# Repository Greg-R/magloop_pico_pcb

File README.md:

#  Printed Circuit Board for Magnetic Loop Antenna Controller

**Please note this repository is no longer active.**

The new repository is here:

(https://github.com/Greg-R/magloop_pico_pcb_2)

Design and fabrication files the Magnetic Loop Antenna Controller printed circuit board.

#  License

Please refer to the LICENSE file included in this repository.

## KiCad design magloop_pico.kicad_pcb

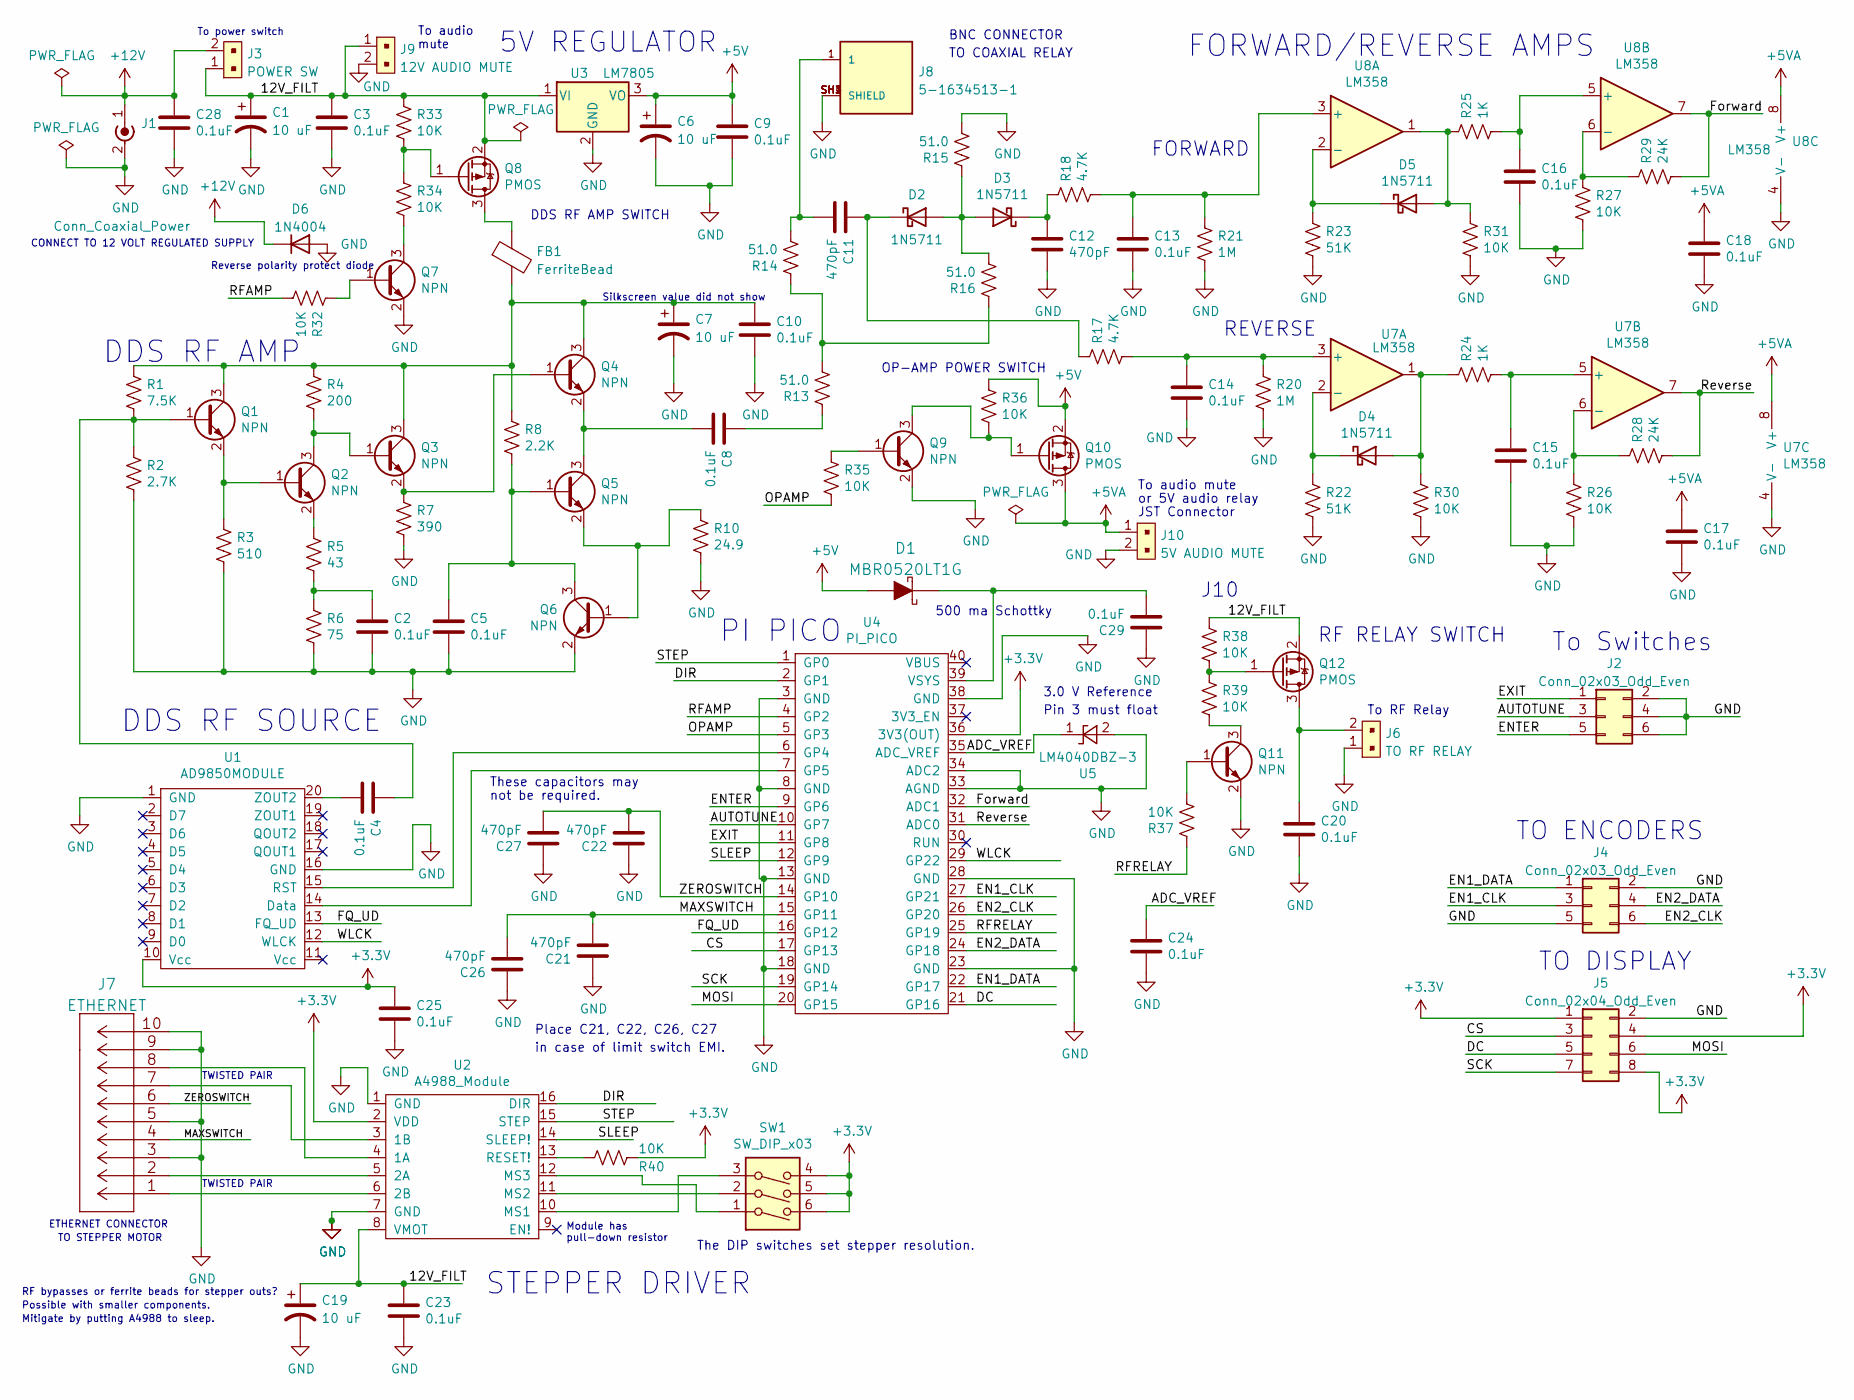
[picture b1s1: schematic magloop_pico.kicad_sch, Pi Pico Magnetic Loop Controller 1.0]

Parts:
C1, C6, C7, C19: 10 uF; CP_Radial_D5.0mm_P2.00mm
C2, C3, C4, C5, C8, C9, C10, C13, C14, C15, C16, C17, C18, C20, C23, C24, C25, C28, C29: 0.1uF; C_1206_3216Metric_Pad1.33x1.80mm_HandSolder
C11, C12, C21, C22, C26, C27: 470pF; C_1206_3216Metric_Pad1.33x1.80mm_HandSolder
D1: MBR0520LT1G; SOD-123; MPN MBR0520LT1G; Digi-Key_PN MBR0520LT1GOSCT-ND
D2, D3, D4, D5: 1N5711; D_DO-35_SOD27_P7.62mm_Horizontal
D6: 1N4004; D_SMB
FB1: FerriteBead; L_1206_3216Metric
J1: Conn_Coaxial_Power; BarrelJack_CUI_PJ-036AH-SMT_Horizontal
J2, J4: Conn_02x03_Odd_Even; IDC-Header_2x03_P2.54mm_Vertical
J3: POWER SW; PinHeader_1x2_P2.5mm_Drill1.1mm; MPN B2B-XH-A(LF)(SN); Digi-Key_PN 455-2247-ND
J5: Conn_02x04_Odd_Even; IDC-Header_2x04_P2.54mm_Vertical
J6: TO RF RELAY; PinHeader_1x2_P2.5mm_Drill1.1mm; MPN B2B-XH-A(LF)(SN); Digi-Key_PN 455-2247-ND
J7: ETHERNET; 2-406541-3
J8: 5-1634513-1; TE_5-1634513-1
J9: 12V AUDIO MUTE; PinHeader_1x2_P2.5mm_Drill1.1mm; MPN B2B-XH-A(LF)(SN); Digi-Key_PN 455-2247-ND
J10: 5V AUDIO MUTE; PinHeader_1x2_P2.5mm_Drill1.1mm; MPN B2B-XH-A(LF)(SN); Digi-Key_PN 455-2247-ND
Q1, Q2, Q3, Q4, Q5, Q6, Q7, Q9, Q11: NPN; SOT-23_Handsoldering
Q8, Q10, Q12: PMOS; SOT-23_Handsoldering
R1: 7.5K; R_1206_3216Metric_Pad1.30x1.75mm_HandSolder
R2: 2.7K; R_1206_3216Metric_Pad1.30x1.75mm_HandSolder
R3: 510; R_1206_3216Metric_Pad1.30x1.75mm_HandSolder
R4: 200; R_1206_3216Metric_Pad1.30x1.75mm_HandSolder
R5: 43; R_1206_3216Metric_Pad1.30x1.75mm_HandSolder
R6: 75; R_1206_3216Metric_Pad1.30x1.75mm_HandSolder
R7: 390; R_1206_3216Metric_Pad1.30x1.75mm_HandSolder
R8: 2.2K; R_1206_3216Metric_Pad1.30x1.75mm_HandSolder
R10: 24.9; R_1206_3216Metric_Pad1.30x1.75mm_HandSolder
R13, R14, R15, R16: 51.0; R_1206_3216Metric_Pad1.30x1.75mm_HandSolder
R17, R18: 4.7K; R_1206_3216Metric_Pad1.30x1.75mm_HandSolder
R20, R21: 1M; R_1206_3216Metric_Pad1.30x1.75mm_HandSolder
R22, R23: 51K; R_1206_3216Metric_Pad1.30x1.75mm_HandSolder
R24, R25: 1K; R_1206_3216Metric_Pad1.30x1.75mm_HandSolder
R26, R27, R30, R31, R32, R33, R34, R35, R36, R37, R38, R39, R40: 10K; R_1206_3216Metric_Pad1.30x1.75mm_HandSolder
R28, R29: 24K; R_1206_3216Metric_Pad1.30x1.75mm_HandSolder
SW1: SW_DIP_x03; DIP-6_W7.62mm
U1: AD9850MODULE; AD9850_MODULE
U2: A4988_Module; A4988_MODULE
U3: LM7805; TO-220-3_Vertical
U4: PI_PICO
U5: LM4040DBZ-3; SOT-23_Handsoldering
U7, U8: LM358; DIP-8_W7.62mm

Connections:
+3V3: C25.1, J5.1, J5.4, J5.8, R40.1, SW1.4, SW1.5, SW1.6, U1.10 (Vcc), U2.2 (VDD), U4.36 (3V3(OUT))
+5V: C6.1, C9.1, D1.A, Q10.2 (S), R36.1, U3.3 (VO)
+5VA: C17.1, C18.1, J10.1, Q10.3 (D), U7.8 (V+), U8.8 (V+)
+12V: C28.1, D6.1 (K), J1.1 (In), J3.2
/12V_FILT: C1.1, C3.1, C19.1, C23.1, J3.1, J9.1, Q8.2 (S), Q12.2 (S), R33.1, R38.1, U2.8 (VMOT), U3.1 (VI)
/ADC_VREF: C24.1, U4.35 (ADC_VREF), U5.1 (K)
/AUTOTUNE: J2.3, U4.10 (GP7)
/CS: J5.3, U4.17 (GP13)
/DC: J5.5, U4.21 (GP16)
/DIR: U2.16 (DIR), U4.2 (GP1)
/EN1_CLK: J4.3, U4.27 (GP21)
/EN1_DATA: J4.1, U4.22 (GP17)
/EN2_CLK: J4.6, U4.26 (GP20)
/EN2_DATA: J4.4, U4.24 (GP18)
/ENTER: J2.5, U4.9 (GP6)
/EXIT: J2.1, U4.11 (GP8)
/FQ_UD: U1.13 (FQ_UD), U4.16 (GP12)
/Forward: R29.2, U4.32 (ADC1), U8.7
/MAXSWITCH: C21.2, C26.2, J7.4, U4.15 (GP11)
/MOSI: J5.6, U4.20 (GP15)
/OPAMP: R35.2, U4.5 (GP3)
/RFAMP: R32.2, U4.4 (GP2)
/RFRELAY: R37.1, U4.25 (GP19)
/Reverse: R28.2, U4.31 (ADC0), U7.7
/SCK: J5.7, U4.19 (GP14)
/SLEEP: U2.14 (SLEEP!), U4.12 (GP9)
/STEP: U2.15 (STEP), U4.1 (GP0)
/WLCK: U1.12 (WLCK), U4.29 (GP22)
/ZEROSWITCH: C22.2, C27.2, J7.6, U4.14 (GP10)
GND: C1.2, C2.2, C3.2, C5.2, C6.2, C7.2, C9.2, C10.2, C12.2, C13.2, C14.2, C15.2, C16.2, C17.2, C18.2, C19.2, C20.2, C21.1, C22.1, C23.2, C24.2, C25.2, C26.1, C27.1, C28.2, C29.1, D6.2 (A), J1.2 (Ext), J2.2, J2.4, J2.6, J4.2, J4.5, J5.2, J6.1, J7.3, J7.5, J7.9, J7.10, J8.SH1 (SHIELD), J8.SH2 (SHIELD), J8.SH3 (SHIELD), J8.SH4 (SHIELD), J9.2, J10.2, Q6.2 (E), Q7.2 (E), Q9.2 (E), Q11.2 (E), R2.2, R3.2, R6.2, R7.2, R10.2, R15.2, R20.2, R21.2, R22.2, R23.2, R26.2, R27.2, R30.2, R31.2, U1.1 (GND), U1.16 (GND), U2.1 (GND), U2.7 (GND), U3.2 (GND), U4.3 (GND), U4.8 (GND), U4.13 (GND), U4.18 (GND), U4.23 (GND), U4.28 (GND), U4.33 (AGND), U4.34 (ADC2), U4.38 (GND), U5.2 (A), U7.4 (V-), U8.4 (V-)
unnamed: C2.1, R5.2, R6.1
unnamed: C4.1, Q1.1 (B), R1.2, R2.1
unnamed: C4.2, U1.20 (ZOUT2)
unnamed: C5.1, Q5.1 (B), Q6.3 (C), R8.2
unnamed: C8.1, R13.1
unnamed: C8.2, Q4.2 (E), Q5.3 (C)
unnamed: C7.1, C10.1, FB1.2, Q1.3 (C), Q3.3 (C), Q4.3 (C), R1.1, R4.1, R8.1
unnamed: C11.1, D2.1 (K), R17.1
unnamed: C11.2, J8.1, R14.2
unnamed: C12.1, D3.1 (K), R18.1
unnamed: C13.1, R18.2, R21.1, U8.3 (+)
unnamed: C14.1, R17.2, R20.1, U7.3 (+)
unnamed: C15.1, R24.2, U7.5 (+)
unnamed: C16.1, R25.2, U8.5 (+)
unnamed: C20.1, J6.2, Q12.3 (D)
unnamed: C29.2, D1.K, U4.39 (VSYS)
unnamed: D2.2 (A), D3.2 (A), R15.1, R16.2
unnamed: D4.1 (K), R22.1, U7.2 (-)
unnamed: D4.2 (A), R24.1, R30.1, U7.1
unnamed: D5.1 (K), R23.1, U8.2 (-)
unnamed: D5.2 (A), R25.1, R31.1, U8.1
unnamed: FB1.1, Q8.3 (D)
unnamed: J7.1, U2.6 (2B)
unnamed: J7.2, U2.5 (2A)
unnamed: J7.7, U2.3 (1B)
unnamed: J7.8, U2.4 (1A)
unnamed: Q1.2 (E), Q2.1 (B), R3.1
unnamed: Q2.2 (E), R5.1
unnamed: Q2.3 (C), Q3.1 (B), R4.2
unnamed: Q3.2 (E), Q4.1 (B), R7.1
unnamed: Q5.2 (E), Q6.1 (B), R10.1
unnamed: Q7.1 (B), R32.1
unnamed: Q7.3 (C), R34.2
unnamed: Q8.1 (G), R33.2, R34.1
unnamed: Q9.1 (B), R35.1
unnamed: Q9.3 (C), Q10.1 (G), R36.2
unnamed: Q11.1 (B), R37.2
unnamed: Q11.3 (C), R39.2
unnamed: Q12.1 (G), R38.2, R39.1
unnamed: R13.2, R14.1, R16.1
unnamed: R26.1, R28.1, U7.6 (-)
unnamed: R27.1, R29.1, U8.6 (-)
unnamed: R40.2, U2.13 (RESET!)
unnamed: SW1.1, U2.12 (MS3)
unnamed: SW1.2, U2.11 (MS2)
unnamed: SW1.3, U2.10 (MS1)
unnamed: U1.14 (Data), U4.7 (GP5)
unnamed: U1.15 (RST), U4.6 (GP4)

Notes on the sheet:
To RF Relay
CONNECT TO 12 VOLT REGULATED SUPPLY
PI PICO
STEPPER DRIVER
To audio mute
JST Connector
The DIP switches set stepper resolution.
BNC CONNECTOR
To Switches
Reverse polarity protect diode
DDS RF AMP SWITCH
or 5V audio relay
TWISTED PAIR
ETHERNET CONNECTOR
Silkscreen value did not show
Module has pull-down resistor
TO STEPPER MOTOR
J10
RF bypasses or ferrite beads for stepper outs?
OP-AMP POWER SWITCH
5V REGULATOR
REVERSE
To audio
To power switch
DDS RF SOURCE
TO COAXIAL RELAY
Place C21, C22, C26, C27
TO ENCODERS
500 ma Schottky
FORWARD
DDS RF AMP
These capacitors may
Possible with smaller components.
TO DISPLAY
Mitigate by putting A4988 to sleep.
FORWARD/REVERSE AMPS
Pin 3 must float
3.0 V Reference
mute
not be required.

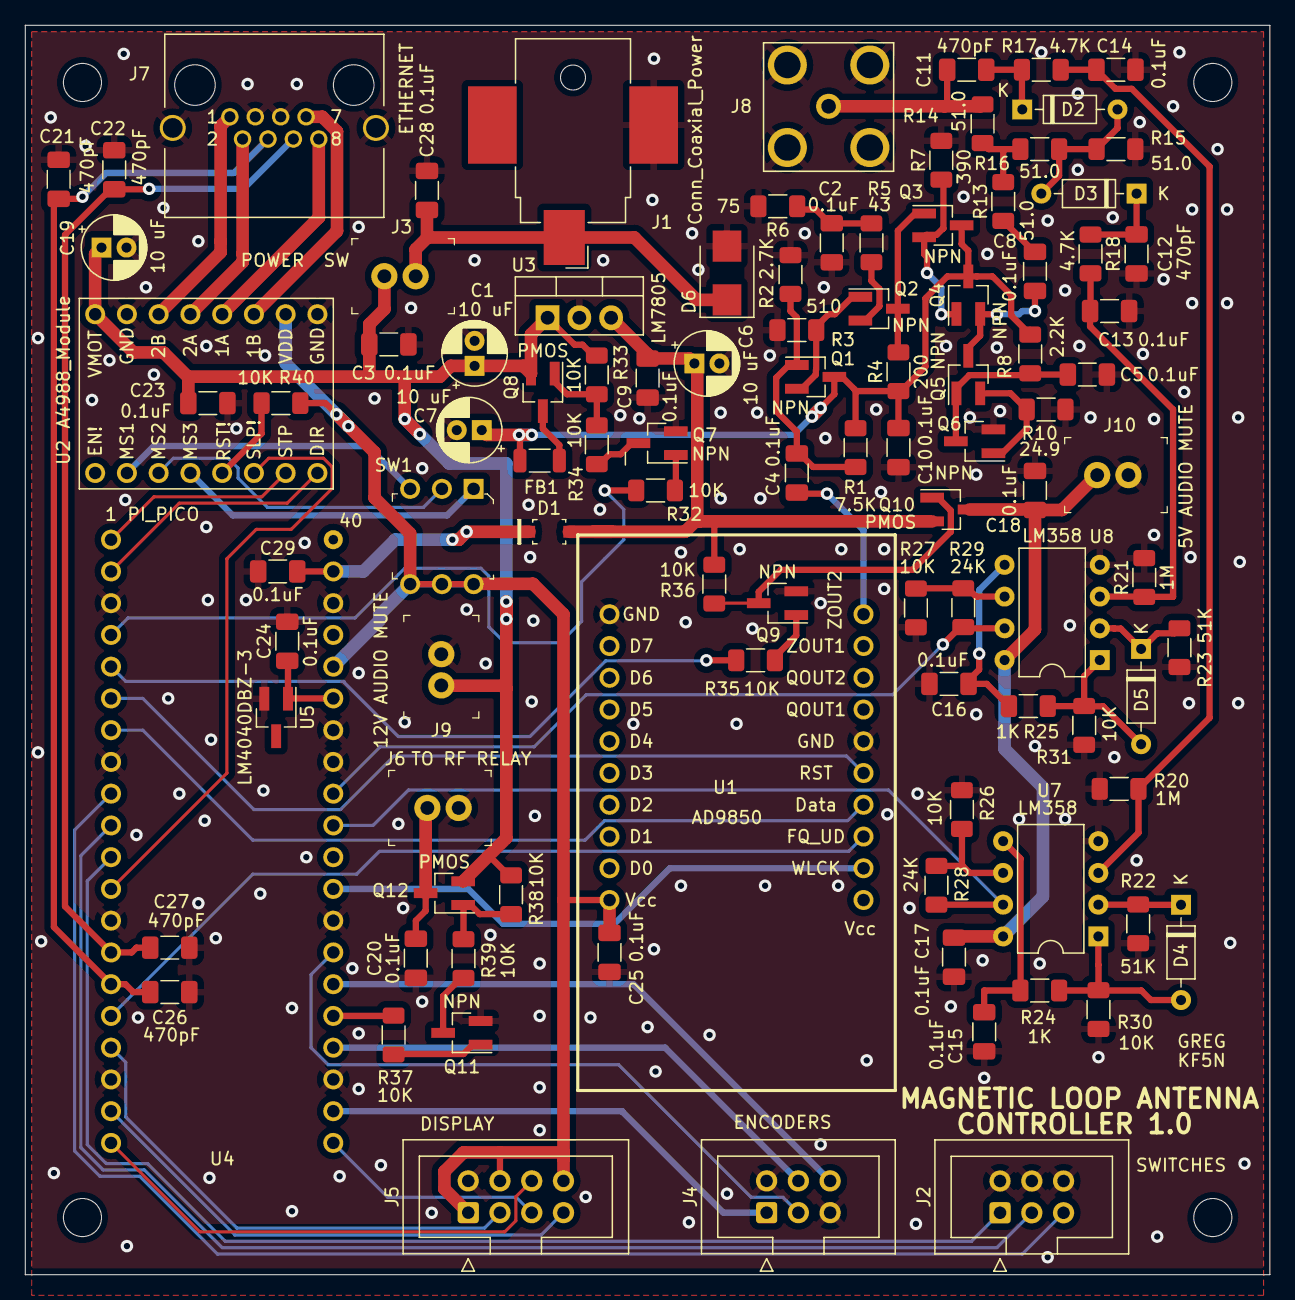
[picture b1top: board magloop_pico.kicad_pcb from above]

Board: 2 copper layers, 99.6 x 99.9 mm, 102 parts (0 on the bottom side), 78 nets.

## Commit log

2022-05-09 Initial commit.
2022-05-15 Added BOM directory
2022-05-17 Added README file.
2022-05-17 Added LICENSE file.
2022-05-17 Modified README file.
2022-05-18 Added schematic PDF.
2022-05-24 Added BOMs from Digikey and Kicad schematic. Minor clean up top metal and changed 50 ohm resistors to 51.
2022-05-28 Added alternative source for BNC connector (eBay).
2022-05-28 A Kicad file got changed.
2023-01-27 Released PCB 1.0
2023-05-23 Clean-up before last update.
2023-05-23 Updated README with link to new repository.
2023-05-23 Updated README to indicate repository is not being updated.

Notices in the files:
parts and their libraries:
Copyright 2021 Accelerated Designs. All rights reserved.
